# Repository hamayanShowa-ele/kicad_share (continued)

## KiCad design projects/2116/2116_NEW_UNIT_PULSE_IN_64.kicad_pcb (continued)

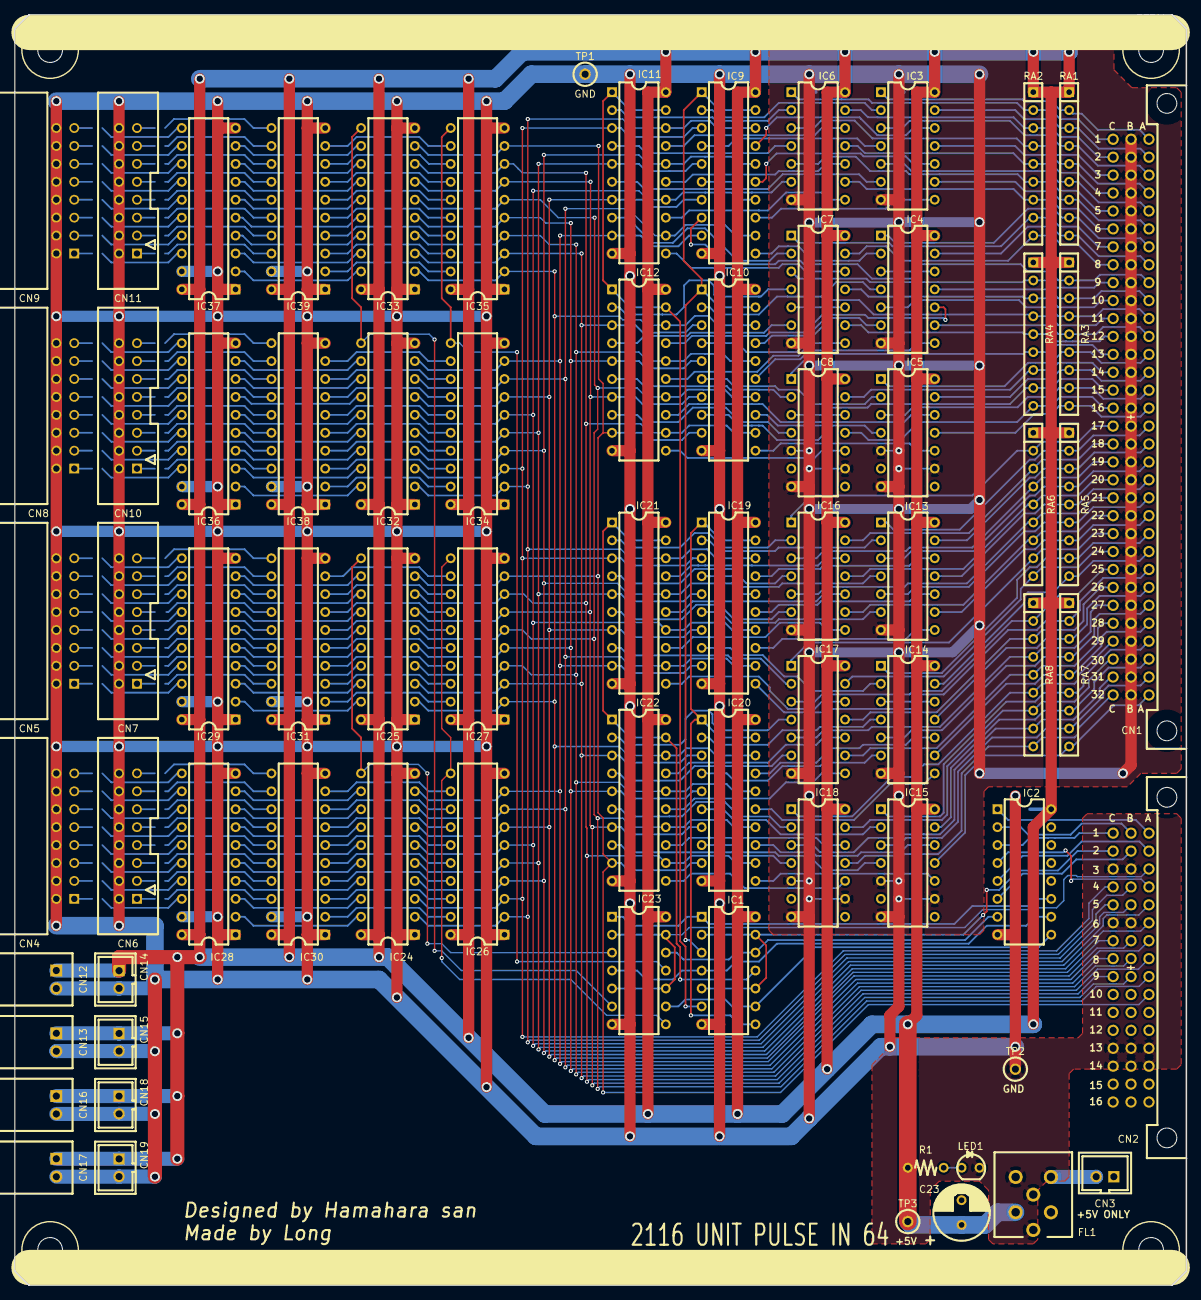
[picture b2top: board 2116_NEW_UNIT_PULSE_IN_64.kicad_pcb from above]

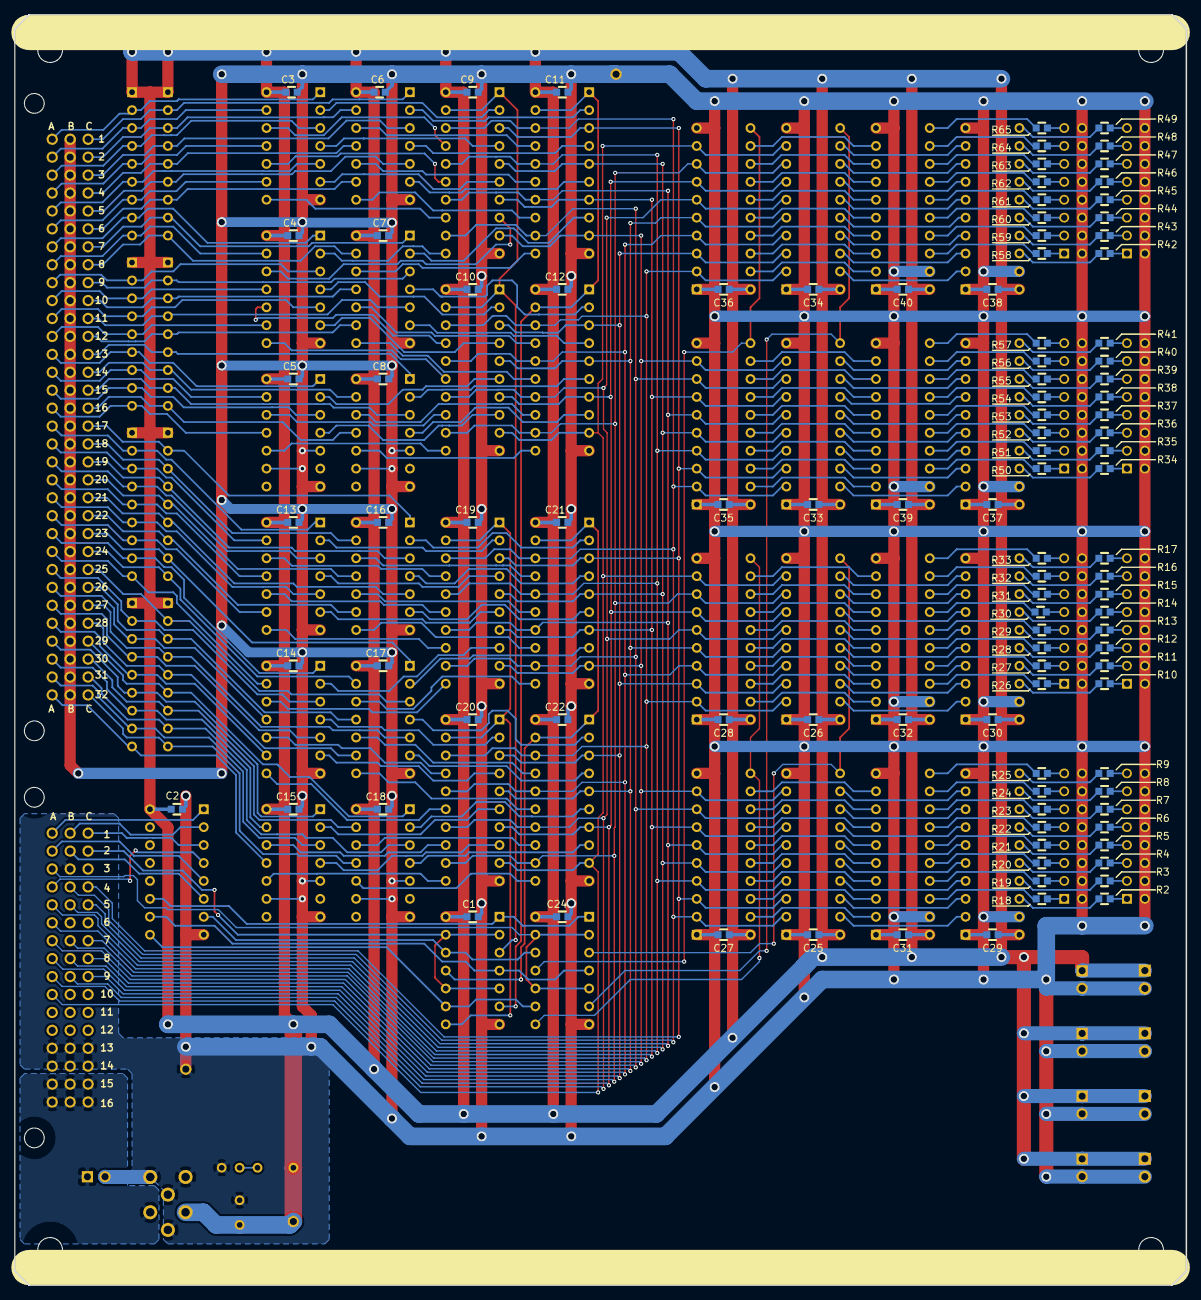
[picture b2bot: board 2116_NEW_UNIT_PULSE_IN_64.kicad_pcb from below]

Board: 2 copper layers, 166.0 x 180.0 mm, 176 parts (103 on the bottom side), 360 nets.

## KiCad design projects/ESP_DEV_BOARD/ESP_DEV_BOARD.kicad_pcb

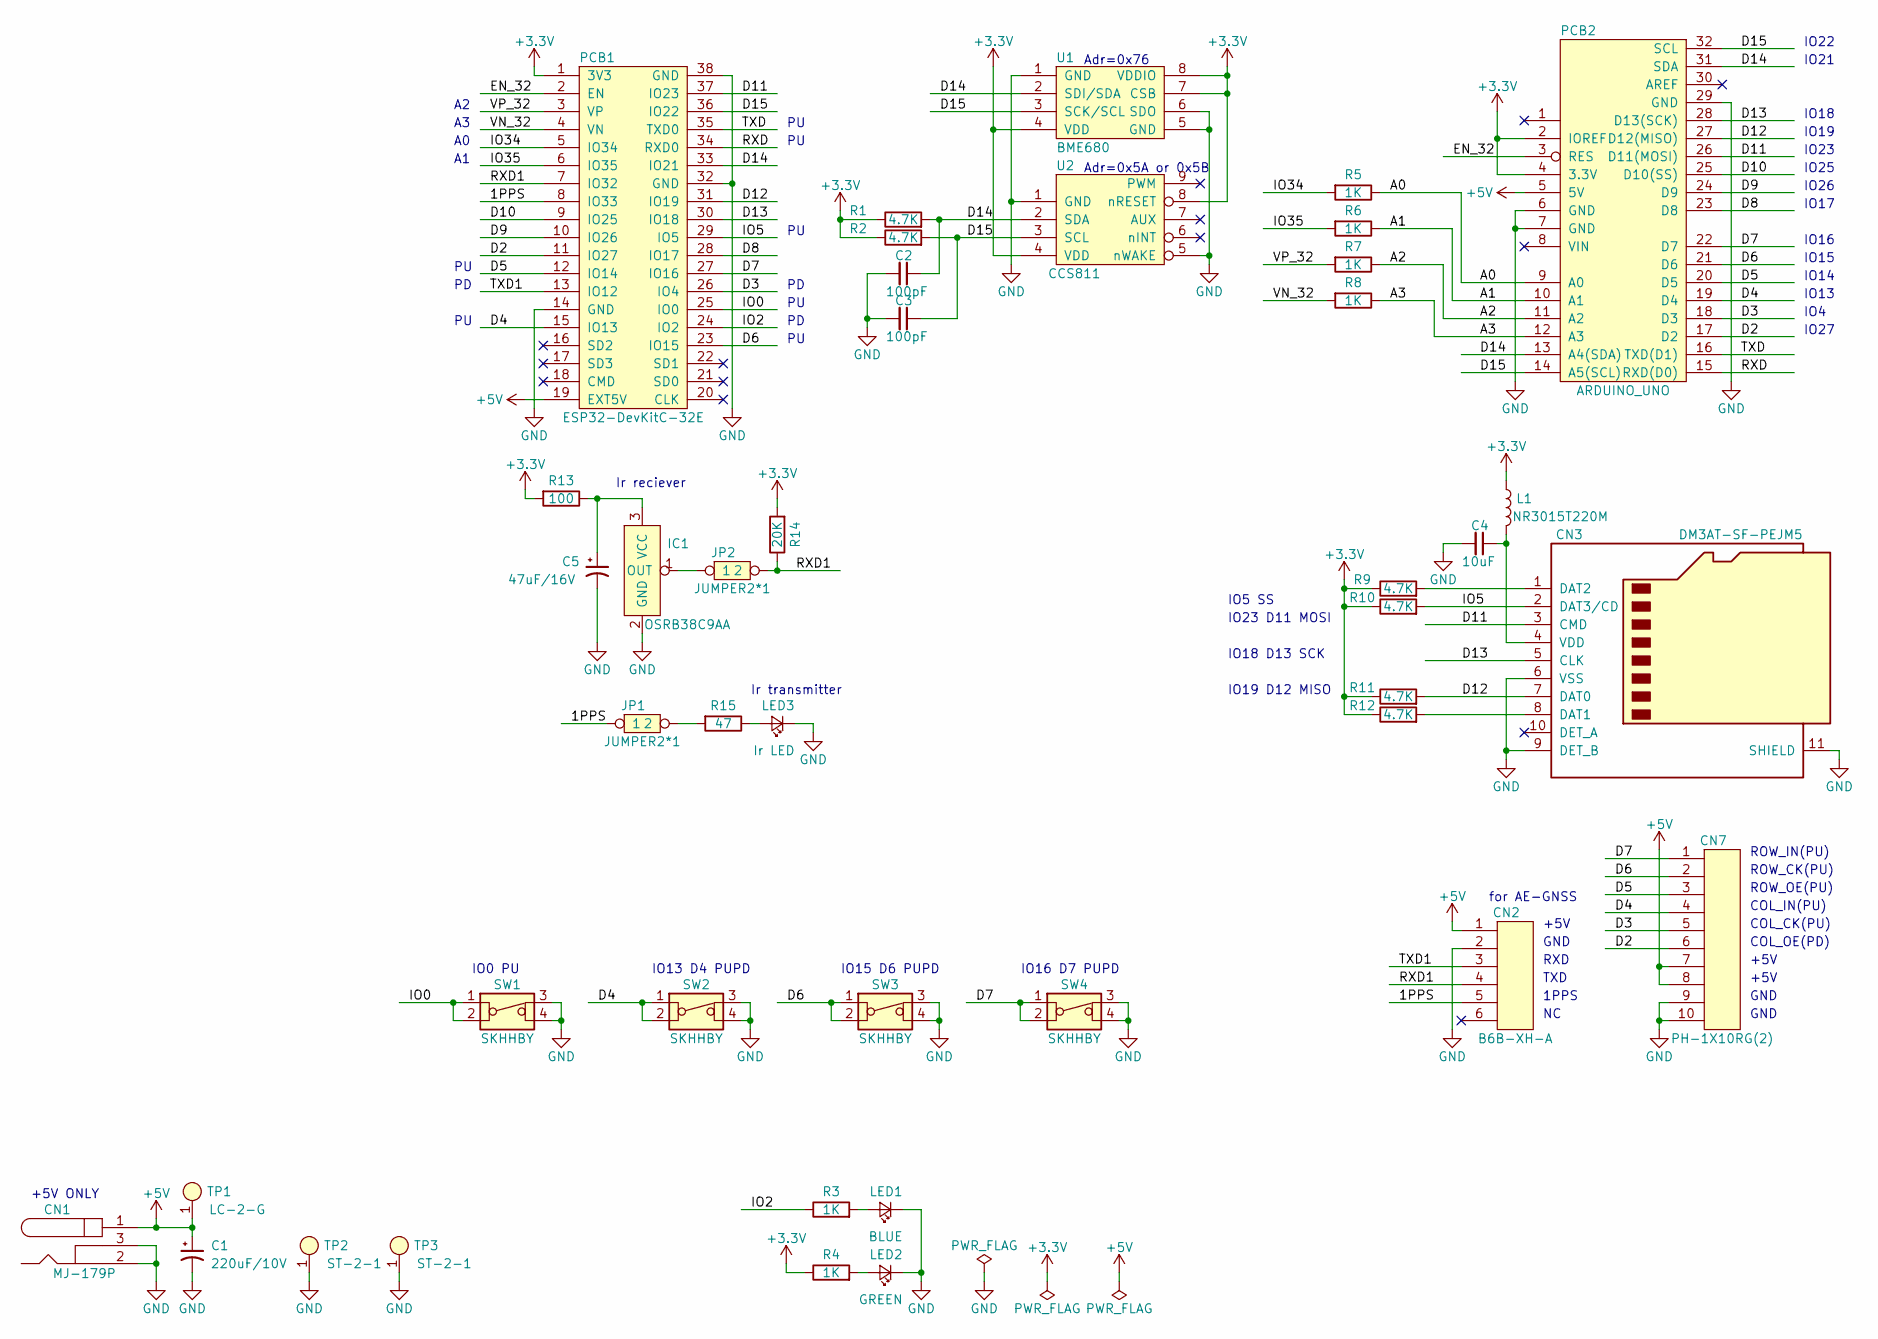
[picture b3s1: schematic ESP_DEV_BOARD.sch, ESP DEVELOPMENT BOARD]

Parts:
C1: 220uF/10V; CP_Radial_D8.25mm_P3.80mm
C2, C3: 100pF; C_0603
C4: 10uF; C_0805
C5: 47uF/16V; CP_Radial_D5.0mm_P2.00mm
CN1: MJ-179P
CN2: B6B-XH-A; cn_B6B-XH-A
CN3: DM3AT-SF-PEJM5; cn_DM3AT-SF-PEJM5
CN7: PH-1X10RG(2); cn_PH-1X10RG_2
IC1: OSRB38C9AA; ic_OSRB38C9AA
JP1, JP2: JUMPER2*1; JP_JUMPER1x2
L1: NR3015T220M; NR3010
LED1: BLUE; C_0603
LED2: GREEN; C_0603
LED3: Ir LED; led_5mmLED
PCB1: ESP32-DevKitC-32E; pcb_ESP32-DevKitC
PCB2: ARDUINO_UNO; pcb_ARDUINO_UNO
R1, R2, R9, R10, R11, R12: 4.7K; C_0603
R3, R4, R5, R6, R7, R8: 1K; C_0603
R13: 100; C_0603
R14: 20K; C_0603
R15: 47; C_0603
SW1, SW2, SW3, SW4: SKHHBY
TP1: LC-2-G
TP2, TP3: ST-2-1; LC-2-G
U1: BME680; pcb_BME680_strawberry-linux
U2: CCS811; pcb_CCS811_strawberry-linux

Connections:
+3V3: L1.1, PCB1.1 (3V3), PCB2.2 (IOREF), PCB2.4 (3.3V), R1.1, R2.1, R4.1, R9.1, R10.1, R11.1, R12.1, R13.2, R14.2, U1.4 (VDD), U1.7 (CSB), U1.8 (VDDIO), U2.4 (VDD), U2.8 (nRESET)
+5V: C1.1, CN1.1, CN2.1, CN7.7, CN7.8, PCB1.19 (EXT5V), PCB2.5 (5V), TP1.1
/1PPS: CN2.5, JP1.1, PCB1.8 (IO33)
/A0: PCB2.9 (A0), R5.1
/A1: PCB2.10 (A1), R6.1
/A2: PCB2.11 (A2), R7.1
/A3: PCB2.12 (A3), R8.1
/D2: CN7.6, PCB1.11 (IO27), PCB2.17 (D2)
/D3: CN7.5, PCB1.26 (IO4), PCB2.18 (D3)
/D4: CN7.4, PCB1.15 (IO13), PCB2.19 (D4), SW2.1, SW2.2
/D5: CN7.3, PCB1.12 (IO14), PCB2.20 (D5)
/D6: CN7.2, PCB1.23 (IO15), PCB2.21 (D6), SW3.1, SW3.2
/D7: CN7.1, PCB1.27 (IO16), PCB2.22 (D7), SW4.1, SW4.2
/D8: PCB1.28 (IO17), PCB2.23 (D8)
/D9: PCB1.10 (IO26), PCB2.24 (D9)
/D10: PCB1.9 (IO25), PCB2.25 (D10(SS))
/D11: CN3.3 (CMD), PCB1.37 (IO23), PCB2.26 (D11(MOSI))
/D12: CN3.7 (DAT0), PCB1.31 (IO19), PCB2.27 (D12(MISO)), R11.2
/D13: CN3.5 (CLK), PCB1.30 (IO18), PCB2.28 (D13(SCK))
/D14: C2.1, PCB1.33 (IO21), PCB2.13 (A4(SDA)), PCB2.31 (SDA), R1.2, U1.2 (SDI/SDA), U2.2 (SDA)
/D15: C3.1, PCB1.36 (IO22), PCB2.14 (A5(SCL)), PCB2.32 (SCL), R2.2, U1.3 (SCK/SCL), U2.3 (SCL)
/EN_32: PCB1.2 (EN), PCB2.3 (RES)
/IO0: PCB1.25 (IO0), SW1.1, SW1.2
/IO2: PCB1.24 (IO2), R3.1
/IO5: CN3.2 (DAT3/CD), PCB1.29 (IO5), R10.2
/IO34: PCB1.5 (IO34), R5.2
/IO35: PCB1.6 (IO35), R6.2
/RXD: PCB1.34 (RXD0), PCB2.15 (RXD(D0))
/RXD1: CN2.4, JP2.2, PCB1.7 (IO32), R14.1
/TXD: PCB1.35 (TXD0), PCB2.16 (TXD(D1))
/TXD1: CN2.3, PCB1.13 (IO12)
/VN_32: PCB1.4 (VN), R8.2
/VP_32: PCB1.3 (VP), R7.2
GND: C1.2, C2.2, C3.2, C4.2, C5.2, CN1.2, CN1.3, CN2.2, CN3.6 (VSS), CN3.9 (DET_B), CN3.11 (SHIELD), CN7.9, CN7.10, IC1.2 (GND), LED1.2 (K), LED2.2 (K), LED3.2 (K), PCB1.14 (GND), PCB1.32 (GND), PCB1.38 (GND), PCB2.6 (GND), PCB2.7 (GND), PCB2.29 (GND), SW1.3, SW1.4, SW2.3, SW2.4, SW3.3, SW3.4, SW4.3, SW4.4, TP2.1, TP3.1, U1.1 (GND), U1.5 (GND), U1.6 (SDO), U2.1 (GND), U2.5 (nWAKE)
unnamed: C4.1, CN3.4 (VDD), L1.2
unnamed: C5.1, IC1.3 (VCC), R13.1
unnamed: CN3.1 (DAT2), R9.2
unnamed: CN3.8 (DAT1), R12.2
unnamed: IC1.1 (OUT), JP2.1
unnamed: JP1.2, R15.2
unnamed: LED1.1 (A), R3.2
unnamed: LED2.1 (A), R4.2
unnamed: LED3.1 (A), R15.1

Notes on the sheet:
+5V ONLY
ROW_IN(PU)
ROW_CK(PU)
ROW_OE(PU)
COL_IN(PU)
COL_CK(PU)
COL_OE(PD)
+5V
GND
IO16
IO22
IO19
IO21
IO18
IO23
IO25
IO26
IO17
IO15
IO14
IO13
IO4
IO27
IO18 D13 SCK
IO19 D12 MISO
IO23 D11 MOSI
IO5 SS
IO16 D7 PUPD
IO15 D6 PUPD
IO13 D4 PUPD
IO0 PU
Adr=0x76
Adr=0x5A or 0x5B
+5V
RXD
TXD
1PPS
for AE-GNSS
Ir reciever
Ir transmitter

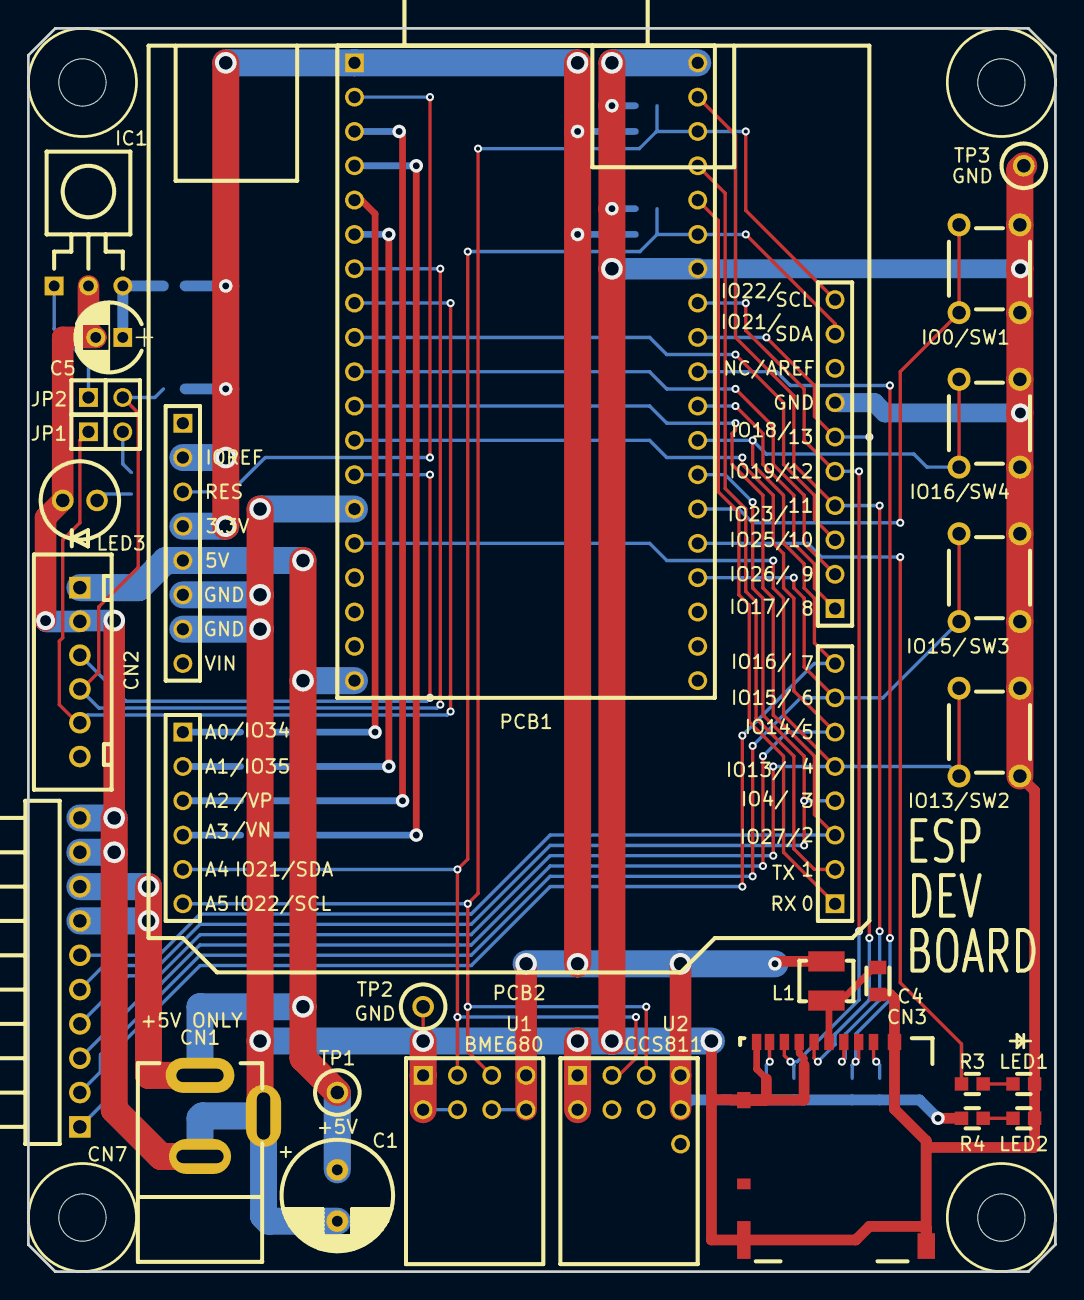
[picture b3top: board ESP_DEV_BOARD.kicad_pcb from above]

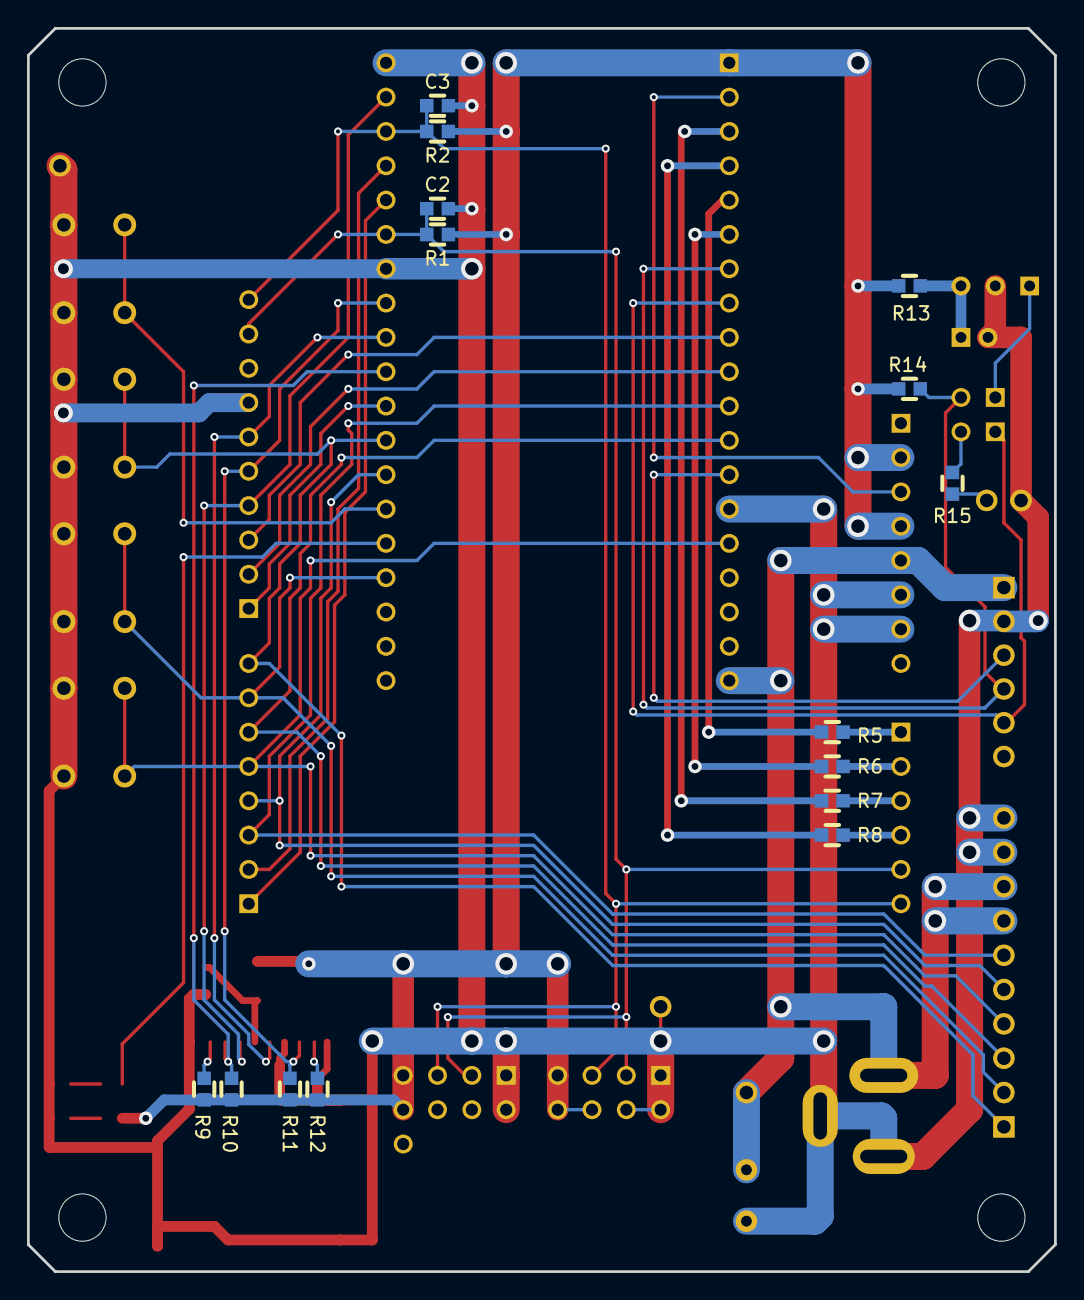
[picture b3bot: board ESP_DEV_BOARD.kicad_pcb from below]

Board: 2 copper layers, 76.0 x 92.0 mm, 42 parts (15 on the bottom side), 43 nets.

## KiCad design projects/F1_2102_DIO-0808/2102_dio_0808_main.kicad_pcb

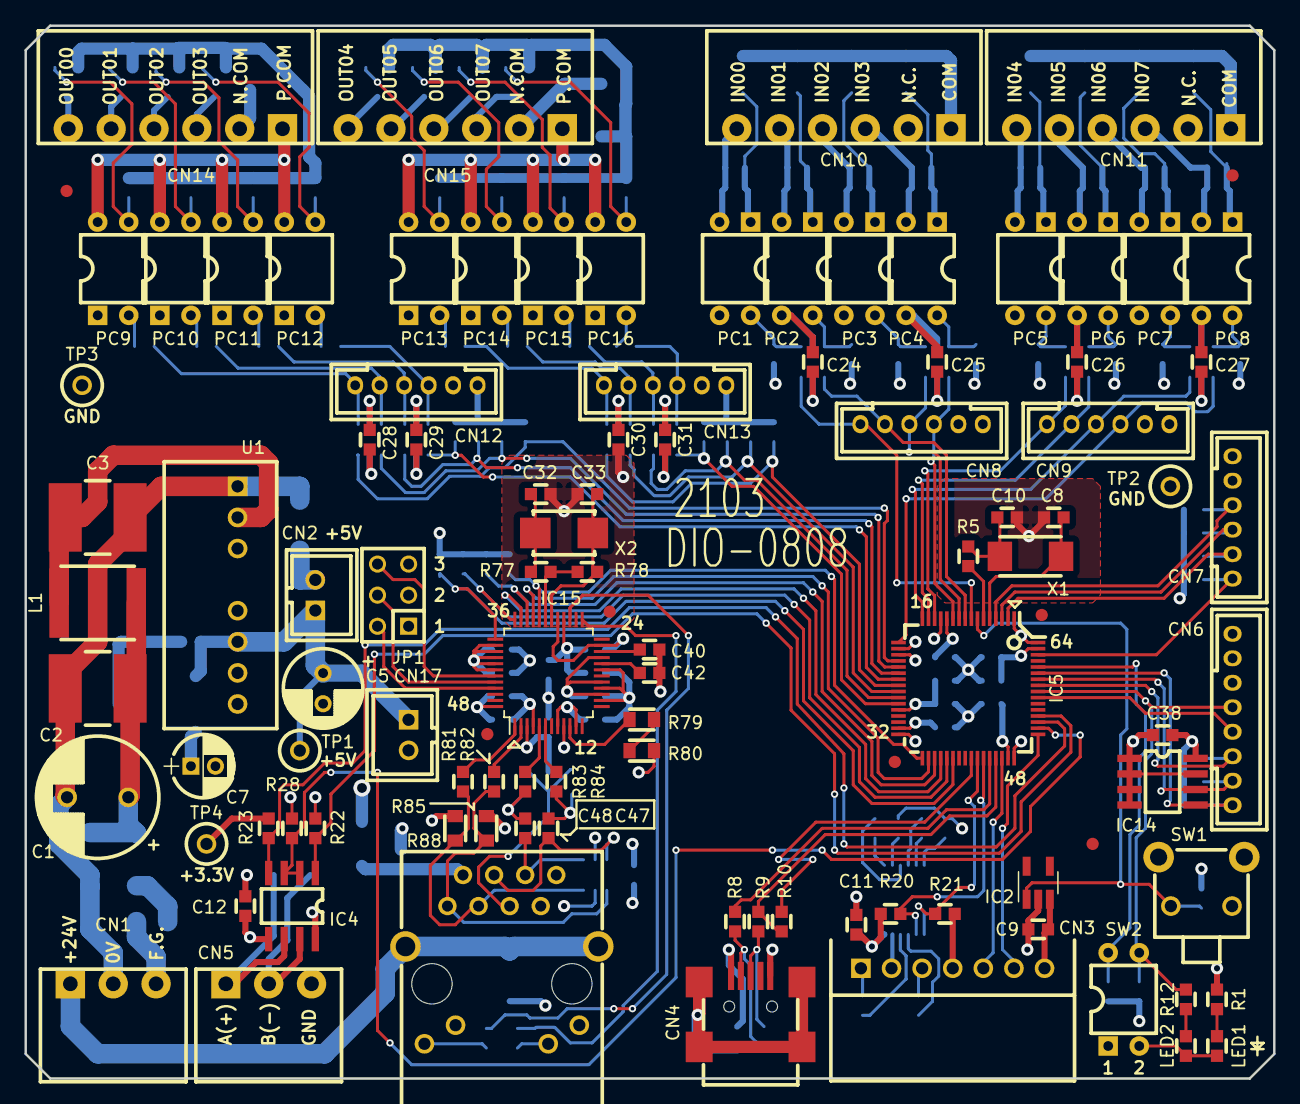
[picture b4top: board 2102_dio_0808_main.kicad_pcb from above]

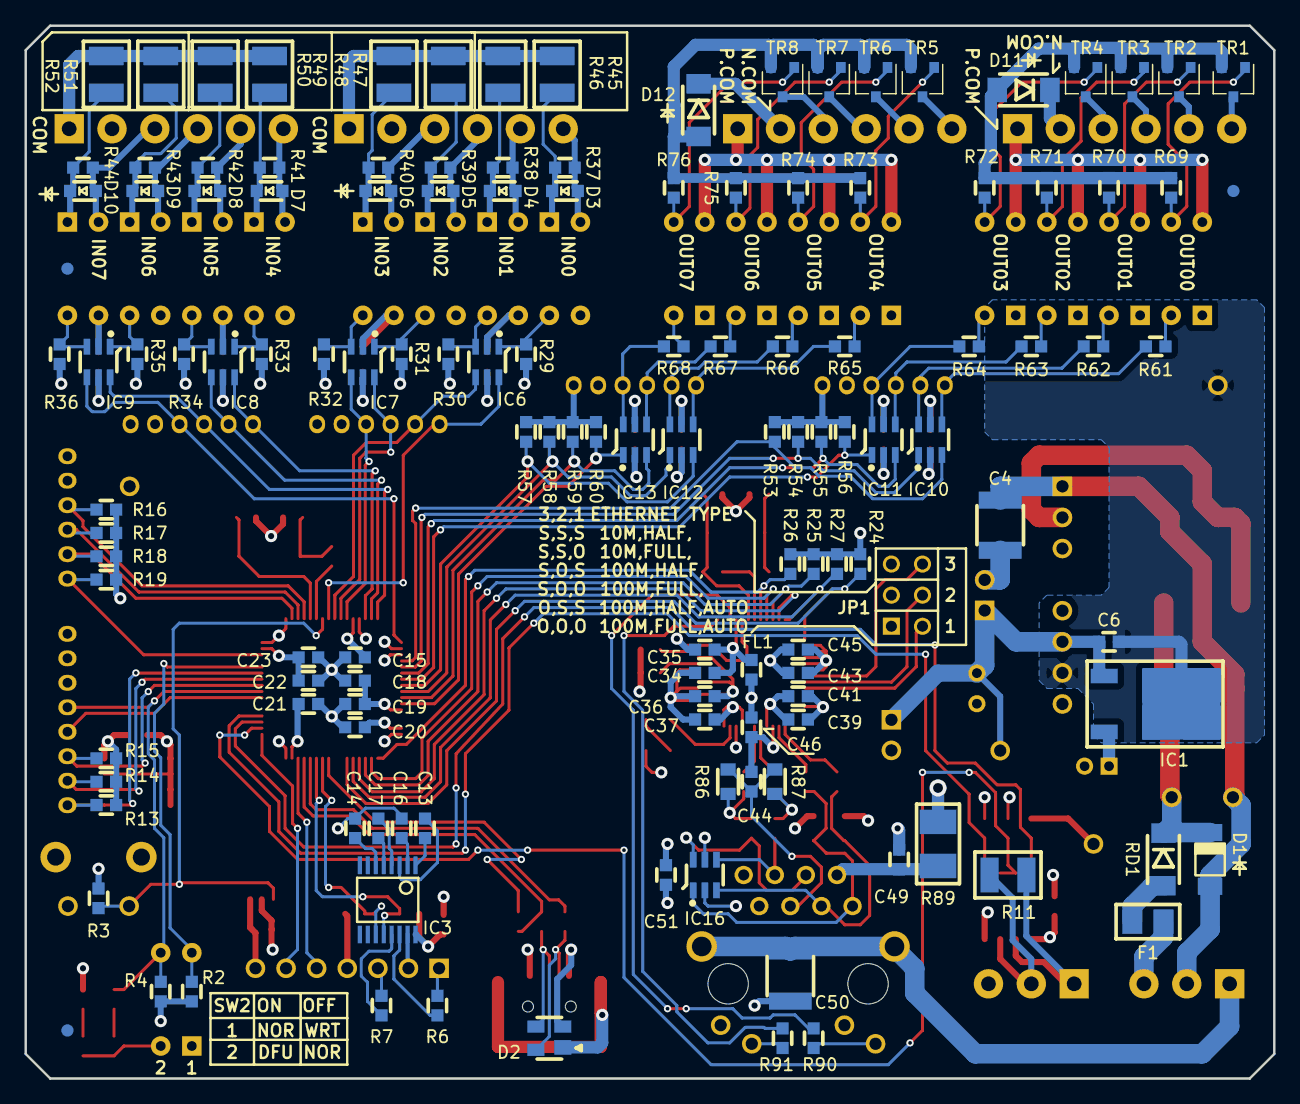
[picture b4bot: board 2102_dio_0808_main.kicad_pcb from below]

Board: 4 copper layers, 102.0 x 86.0 mm, 227 parts (130 on the bottom side), 164 nets.

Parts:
C1: 470uF/35V; CP_Radial_D10.0mm_P5.00mm
C2, C3: 22uF/50V; c_KRM55TR71H226MH01K
C4: 150pF/3KV; c_4532
C5: 220uF/10V; CP_Radial_D6.50mm_P2.50mm
C6, C11, C12, C13, C14, C15, C16, C17, C18, C19, C20, C21, C22, C24, C25, C26, C27, C28, C29, C30, C31, C35, C36, C37, C38, C39, C41, C43, C45, C51: 0.1uF; C_0603
C7: 22uF/16V; CP_Radial_D5.0mm_P2.00mm
C8, C10: 10pF; C_0603
C9: 1uF; C_0603
C23, C34, C42, C46: 4.7uF; C_0603
C32, C33: 13pF; C_0603
C40, C44: 0.01uF; C_0603
C47, C48: 6800pF; C_0603
C49: 22000pF; C_0603
C50: 1000pF/3kV; c_4532
CN1, CN5: 1844223; cn_1844223
CN2, CN17: B2B-XH-A; cn_B2B-XH-A
CN3: S7B-XH-A; cn_S7B-XH-A
CN4: UX60A-MB-5ST; cn_UX60-MB-5ST
CN6: B8B-PH-K-S; cn_B8B-PH-K-S
CN7, CN8, CN9, CN12, CN13: B6B-PH-K-S; cn_B6B-PH-K-S
CN10, CN11, CN14, CN15: 1844252; cn_1844252
CN16: J1B1211CCD
D1, D11, D12: SX34F; d_SX34F
D2: SP0503BAHTG; d_SP0503BAHT
D3, D4, D5, D6, D7, D8, D9, D10: 1SS355; d_1SS355
F1: 0.25A; C_3216
FL1: BLM18PG121SN1D; C_0603
IC1: NJM2391DL1; TO-252-2
IC2: PST8228NR; SOT-23-5_HandSoldering
IC3: ICL3232CVZ; IC_TSSOP-16
IC4: ISL83485IBZ; SOIC-8
IC5: STM32F103RET; ic_LQFP-64_10x10mm_Pitch0.5mm
IC6, IC7, IC8, IC9, IC10, IC11, IC12, IC13: SN74LVC2G14DBVR; SOT-23-6
IC14: 24AA025E48T; SOIC-8
IC15: W5500; ic_LQFP-48_7x7mm_Pitch0.5mm
IC16: TPD4E1U06DBVR; SOT-23-6
JP1: JUMPER 2*6; jp_JUMPER3x2
L1: 3uH; l_NR6028
LED1: GREEN; C_0603
LED2: BLUE; C_0603
PC1, PC2, PC3, PC4, PC5, PC6, PC7, PC8, PC9, PC10, PC11, PC12, PC13, PC14, PC15, PC16: VO618A-4X016; ic_DIP-4_W7.62mm
R1, R90, R91: 470; C_0603
R2, R3, R4, R13, R14, R15: 4.7K; C_0603
R5, R77, R81, R82, R83, R84: 0; C_0603
R6, R7: 100; C_0603
R8, R9: 27; C_0603
R10: 1.5K; C_0603
R11: 100; RGC325
R12: 1K; C_0603
R16, R17, R18, R19, R20, R21, R22, R23, R24, R25, R26, R27, R69, R70, R71, R72, R73, R74, R75, R76: 10K; C_0603
R28, R53, R54, R55, R56, R57, R58, R59, R60: 100K; C_0603
R29, R30, R31, R32, R33, R34, R35, R36: 3.3K; C_0603
R37, R38, R39, R40, R41, R42, R43, R44: 2.7K; C_0603
R45, R46, R47, R48, R49, R50, R51, R52: 15K; RGC325
R61, R62, R63, R64, R65, R66, R67, R68: 1.2K; C_0603
R78: 1M; C_0603
R79: 12K; C_0805
R80: 300; C_0805
R85, R88: 49.9; C_0805
R86, R87: 82; C_0805
R89: 10 1/4W; r_RGC3528
RD1: PDZVTFTR33B; SOD128
SW1: EQV-PC305K; sw_EQVPC
SW2: A6TR-2104; ic_DIP-4_W7.62mm
TP1, TP4: LC-2-G
TP2, TP3: ST-2-1; LC-2-G
TR1, TR2, TR3, TR4, TR5, TR6, TR7, TR8: 2SC3325; SC-59
U1: RSE-2405SZ/H2; u_RSE-2405SZ_H2
X1: NX5032GA 8MHz; x_NX5032GA
X2: ABM3-25.000MHz; x_ABM3-25M

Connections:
+3.3VA: C36.1, C37.1, C39.1, C41.1, C43.1, C45.1, C46.1, C51.1, CN16.10, CN16.12, FL1.2, IC15.4, IC15.8, IC15.11, IC15.15, IC15.17, IC15.21, IC16.5, R85.1, R88.1, R89.1
+3V3: C7.1, C9.1, C11.1, C12.1, C15.1, C18.1, C19.1, C20.1, C21.1, C22.1, C23.1, C24.1, C25.1, C26.1, C27.1, C28.1, C29.1, C30.1, C31.1, C34.1, C35.1, C38.1, CN3.4, CN6.7, CN7.5, CN8.5, CN9.5, CN12.5, CN13.5, FL1.1, IC1.3, IC2.2, IC3.16, IC4.8, IC5.1, IC5.13, IC5.19, IC5.32, IC5.48, IC5.64, IC6.5, IC7.5, IC8.5, IC9.5, IC10.5, IC11.5, IC12.5, IC13.5, IC14.8, IC15.28, PC9.1, PC10.1, PC11.1, PC12.1, PC13.1, PC14.1, PC15.1, PC16.1, R1.1, R2.1, R3.1, R4.1, R13.1, R14.1, R15.1, R16.1, R17.1, R18.1, R19.1, R20.1, R21.1, R22.1, R23.1, R24.1, R25.1, R26.1, R27.1, R29.1, R30.1, R31.1, R32.1, R33.1, R34.1, R35.1, R36.1, TP4.1
+5V: C5.1, C6.1, CN2.1, CN17.1, IC1.1, TP1.1, U1.6
/ETHERNET/ACTLED: IC15.27, R90.1
/ETHERNET/LINKLED: IC15.25, R91.1
/ETHERNET/PMODE0: IC15.45, JP1.6
/ETHERNET/PMODE1: IC15.44, JP1.5
/ETHERNET/PMODE2: IC15.43, JP1.4
/ETHERNET/RD+: C47.1, CN16.4, IC16.6
/ETHERNET/RD-: C48.1, CN16.6, IC16.4
/ETHERNET/RXN: C48.2, R83.2, R87.2
/ETHERNET/RXP: C47.2, R84.2, R86.2
/ETHERNET/SCL1: CN6.2, IC5.58, IC14.6, R14.2
/ETHERNET/SDA1: CN6.1, IC5.59, IC14.5, R13.2
/ETHERNET/SPI2_MISO: IC5.35, IC15.34, R25.2
/ETHERNET/SPI2_MOSI: IC5.36, IC15.35
/ETHERNET/SPI2_SCK: IC5.34, IC15.33
/ETHERNET/TXN: CN16.3, IC16.3, R81.2, R88.2
/ETHERNET/TXP: CN16.1, IC16.1, R82.2, R85.2
/ETHERNET/W5500_CS: IC5.33, IC15.32, R26.2
/ETHERNET/W5500_INT: IC5.37, IC15.36, R27.2
/ETHERNET/W5500_RST: IC5.38, IC15.37, R24.2
/PULSE_INPUT/IN00: CN8.1, IC5.8, IC6.6
/PULSE_INPUT/IN01: CN8.2, IC5.9, IC6.4
/PULSE_INPUT/IN02: CN8.3, IC5.10, IC7.6
/PULSE_INPUT/IN03: CN8.4, IC5.11, IC7.4
/PULSE_INPUT/IN04: CN9.1, IC5.14, IC8.6
/PULSE_INPUT/IN05: CN9.2, IC5.15, IC8.4
/PULSE_INPUT/IN06: CN9.3, IC5.16, IC9.6
/PULSE_INPUT/IN07: CN9.4, IC5.17, IC9.4
/PULSE_INPUT/PCIN00: IC6.1, PC1.4, R29.2
/PULSE_INPUT/PCIN01: IC6.3, PC2.4, R30.2
/PULSE_INPUT/PCIN02: IC7.1, PC3.4, R31.2
/PULSE_INPUT/PCIN03: IC7.3, PC4.4, R32.2
/PULSE_INPUT/PCIN04: IC8.1, PC5.4, R33.2
/PULSE_INPUT/PCIN05: IC8.3, PC6.4, R34.2
/PULSE_INPUT/PCIN06: IC9.1, PC7.4, R35.2
/PULSE_INPUT/PCIN07: IC9.3, PC8.4, R36.2
/PULSE_INPUT/PIN00: CN10.6, D3.1, PC1.2, R37.2
/PULSE_INPUT/PIN01: CN10.5, D4.1, PC2.2, R38.2
/PULSE_INPUT/PIN02: CN10.4, D5.1, PC3.2, R39.2
/PULSE_INPUT/PIN03: CN10.3, D6.1, PC4.2, R40.2
/PULSE_INPUT/PIN04: CN11.6, D7.1, PC5.2, R41.2
/PULSE_INPUT/PIN05: CN11.5, D8.1, PC6.2, R42.2
/PULSE_INPUT/PIN06: CN11.4, D9.1, PC7.2, R43.2
/PULSE_INPUT/PIN07: CN11.3, D10.1, PC8.2, R44.2
/PULSE_OUTPUT/NOUT00: CN12.1, IC10.4, R61.1
/PULSE_OUTPUT/NOUT01: CN12.2, IC10.6, R62.1
/PULSE_OUTPUT/NOUT02: CN12.3, IC11.4, R63.1
/PULSE_OUTPUT/NOUT03: CN12.4, IC11.6, R64.1
/PULSE_OUTPUT/NOUT04: CN13.1, IC12.4, R65.1
/PULSE_OUTPUT/NOUT05: CN13.2, IC12.6, R66.1
/PULSE_OUTPUT/NOUT06: CN13.3, IC13.4, R67.1
/PULSE_OUTPUT/NOUT07: CN13.4, IC13.6, R68.1
/PULSE_OUTPUT/OUT00: IC5.20, IC10.3, R53.2
/PULSE_OUTPUT/OUT01: IC5.21, IC10.1, R54.2
/PULSE_OUTPUT/OUT02: IC5.22, IC11.3, R55.2
/PULSE_OUTPUT/OUT03: IC5.23, IC11.1, R56.2
/PULSE_OUTPUT/OUT04: IC5.24, IC12.3, R57.2
/PULSE_OUTPUT/OUT05: IC5.25, IC12.1, R58.2
/PULSE_OUTPUT/OUT06: IC5.26, IC13.3, R59.2
/PULSE_OUTPUT/OUT07: IC5.27, IC13.1, R60.2
/PULSE_OUTPUT/POUT00: CN14.6, TR1.3
/PULSE_OUTPUT/POUT01: CN14.5, TR2.3
/PULSE_OUTPUT/POUT02: CN14.4, TR3.3
/PULSE_OUTPUT/POUT03: CN14.3, TR4.3
/PULSE_OUTPUT/POUT04: CN15.6, TR5.3
/PULSE_OUTPUT/POUT05: CN15.5, TR6.3
/PULSE_OUTPUT/POUT06: CN15.4, TR7.3
/PULSE_OUTPUT/POUT07: CN15.3, TR8.3
/STM32F103xxx/ACT_LED: CN6.5, IC5.56, R4.2, R12.2, SW2.3
/STM32F103xxx/BOOT0: IC5.60, R2.2, SW2.4
/STM32F103xxx/DIO0: CN7.1, IC5.62, R19.2
/STM32F103xxx/DIO1: CN7.2, IC5.2, R18.2
/STM32F103xxx/DIO2: CN7.3, IC5.3, R17.2
/STM32F103xxx/DIO3: CN7.4, IC5.4, R16.2
/STM32F103xxx/LCD_RES: CN6.3, IC5.57, R15.2
/STM32F103xxx/OSC_IN: C8.1, IC5.5, X1.1
/STM32F103xxx/OSC_OUT: IC5.6, R5.1
/STM32F103xxx/RED_LED: CN6.4, IC5.55
/STM32F103xxx/RS_RXD1: IC3.13, R7.2
/STM32F103xxx/RS_TXD1: IC3.14, R6.2
/STM32F103xxx/RTS4: IC4.2, IC4.3, IC5.50, R28.2
/STM32F103xxx/RXD1: IC3.12, IC5.43, R20.2
/STM32F103xxx/RXD4: IC4.1, IC5.52, R22.2
/STM32F103xxx/SWCLK: CN3.6, IC5.49
/STM32F103xxx/SWDIO: CN3.5, IC5.46
/STM32F103xxx/TRX+: CN5.1, IC4.6, R11.1
/STM32F103xxx/TRX-: CN5.2, IC4.7, R11.2
/STM32F103xxx/TXD1: IC3.11, IC5.42, R21.2
/STM32F103xxx/TXD4: IC4.4, IC5.51, R23.2
/STM32F103xxx/USBDM: IC5.44, R8.2
/STM32F103xxx/USBDP: IC5.45, R9.2, R10.1
/STM32F103xxx/USBON: IC5.41, R10.2
/STM32F103xxx/nRESET: IC2.1, IC5.7, R3.2, SW1.1
Earth: C50.1, CN1.1, CN16.13, CN16.14
GND: C4.2, C5.2, C6.2, C7.2, C8.2, C9.2, C10.2, C11.2, C12.2, C14.2, C15.2, C16.2, C18.2, C19.2, C20.2, C21.2, C22.2, C23.2, C24.2, C25.2, C26.2, C27.2, C28.2, C29.2, C30.2, C31.2, C32.2, C33.2, C34.2, C35.2, C36.2, C37.2, C38.2, C39.2, C40.2, C41.2, C42.2, C43.2, C44.2, C45.2, C46.2, C49.2, C50.2, C51.2, CN2.2, CN3.2, CN3.7, CN4.5, CN5.3, CN6.8, CN7.6, CN8.6, CN9.6, CN12.6, CN13.6, CN16.8, CN17.2, IC1.2, IC2.3, IC3.15, IC4.5, IC5.12, IC5.18, IC5.28, IC5.31, IC5.47, IC5.63, IC6.2, IC7.2, IC8.2, IC9.2, IC10.2, IC11.2, IC12.2, IC13.2, IC14.1, IC14.2, IC14.3, IC14.4, IC14.7, IC15.3, IC15.9, IC15.14, IC15.16, IC15.19, IC15.23, IC15.29, IC15.38, IC15.39, IC15.40, IC15.41, IC15.42, IC15.48, IC16.2, JP1.1, JP1.2, JP1.3, LED1.2, LED2.2, PC1.3, PC2.3, PC3.3, PC4.3, PC5.3, PC6.3, PC7.3, PC8.3, R28.1, R53.1, R54.1, R55.1, R56.1, R57.1, R58.1, R59.1, R60.1, R80.2, SW1.2, SW2.1, SW2.2, TP2.1, TP3.1, U1.7
unnamed: C1.1, C2.1, D1.2, L1.1, RD1.2
unnamed: C1.2, C2.2, C3.2, C4.1, CN1.2, RD1.1, U1.1
unnamed: C3.1, L1.2, U1.2
unnamed: C10.1, R5.2, X1.2
unnamed: C13.1, IC3.1
unnamed: C13.2, IC3.3
unnamed: C14.1, IC3.6
unnamed: C16.1, IC3.2
unnamed: C17.1, IC3.4
unnamed: C17.2, IC3.5
unnamed: C32.1, R77.2, X2.1
unnamed: C33.1, IC15.30, R78.2, X2.2
unnamed: C40.1, IC15.22
unnamed: C42.1, IC15.20
unnamed: C44.1, CN16.5, R86.1, R87.1
unnamed: C49.1, CN16.2, R89.2
unnamed: CN1.3, F1.1
unnamed: CN3.1, R6.1
unnamed: CN3.3, R7.1
unnamed: CN4.1, D2.2
unnamed: CN4.2, D2.4, R8.1
unnamed: CN4.3, D2.3, R9.1
unnamed: CN4.6, D2.1
unnamed: CN10.1, R45.2, R46.2, R47.2, R48.2
unnamed: CN11.1, R49.2, R50.2, R51.2, R52.2
unnamed: CN14.1, PC9.4, PC10.4, PC11.4, PC12.4
unnamed: CN14.2, D11.2
unnamed: CN15.1, PC13.4, PC14.4, PC15.4, PC16.4
unnamed: CN15.2, D12.2
unnamed: CN16.9, R90.2
unnamed: CN16.11, R91.2
unnamed: D1.1, F1.2
unnamed: D3.2, PC1.1, R37.1, R45.1
unnamed: D4.2, PC2.1, R38.1, R46.1
unnamed: D5.2, PC3.1, R39.1, R47.1
unnamed: D6.2, PC4.1, R40.1, R48.1
unnamed: D7.2, PC5.1, R41.1, R49.1
unnamed: D8.2, PC6.1, R42.1, R50.1
unnamed: D9.2, PC7.1, R43.1, R51.1
unnamed: D10.2, PC8.1, R44.1, R52.1
unnamed: D11.1, R69.2, R70.2, R71.2, R72.2, TR1.2, TR2.2, TR3.2, TR4.2
unnamed: D12.1, R73.2, R74.2, R75.2, R76.2, TR5.2, TR6.2, TR7.2, TR8.2
unnamed: IC15.1, R81.1
unnamed: IC15.2, R82.1
unnamed: IC15.5, R83.1
unnamed: IC15.6, R84.1
unnamed: IC15.10, R79.1
unnamed: IC15.31, R77.1, R78.1
unnamed: LED1.1, R1.2
unnamed: LED2.1, R12.1
unnamed: PC9.2, R61.2
unnamed: PC9.3, R69.1, TR1.1
unnamed: PC10.2, R62.2
unnamed: PC10.3, R70.1, TR2.1
unnamed: PC11.2, R63.2
unnamed: PC11.3, R71.1, TR3.1
unnamed: PC12.2, R64.2
unnamed: PC12.3, R72.1, TR4.1
unnamed: PC13.2, R65.2
unnamed: PC13.3, R73.1, TR5.1
unnamed: PC14.2, R66.2
unnamed: PC14.3, R74.1, TR6.1
unnamed: PC15.2, R67.2
unnamed: PC15.3, R75.1, TR7.1
unnamed: PC16.2, R68.2
unnamed: PC16.3, R76.1, TR8.1
unnamed: R79.2, R80.1

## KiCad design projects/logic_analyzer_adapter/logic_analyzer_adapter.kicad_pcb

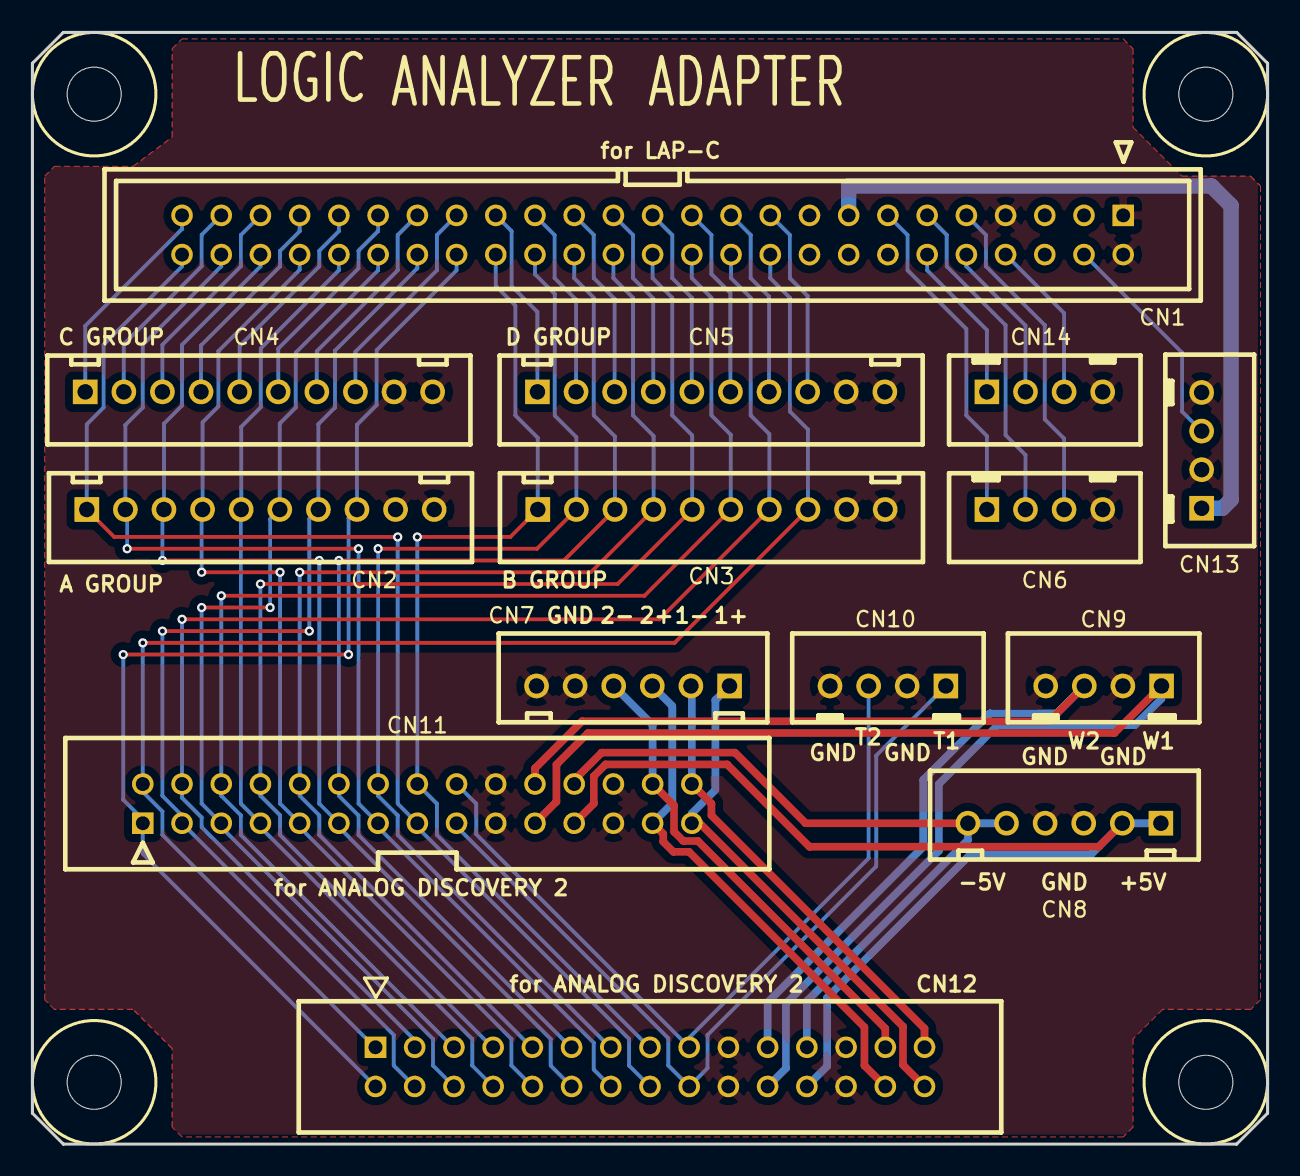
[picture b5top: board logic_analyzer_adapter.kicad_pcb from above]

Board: 2 copper layers, 80.0 x 72.0 mm, 14 parts (1 on the bottom side), 51 nets.

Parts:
CN1: LAP-C 50pin; cn_HIF3FC-50PA-2.54DSA
CN2, CN3, CN4, CN5: B10B-XH-A; cn_B10B-XH-A
CN6, CN9, CN10, CN13, CN14: B4B-XH-A; cn_B4B-XH-A
CN7, CN8: B6B-XH-A; cn_B6B-XH-A
CN11, CN12: DISCOVERY 30Pin; cn_HIF3FC-30PA-254DSA

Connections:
/A0: CN1.50, CN2.1, CN11.15, CN12.16
/A1: CN1.48, CN2.2, CN11.13, CN12.14
/A2: CN1.46, CN2.3, CN11.11, CN12.12
/A3: CN1.44, CN2.4, CN11.9, CN12.10
/A4: CN1.42, CN2.5, CN11.7, CN12.8
/A5: CN1.40, CN2.6, CN11.5, CN12.6
/A6: CN1.38, CN2.7, CN11.3, CN12.4
/A7: CN1.36, CN2.8, CN11.1, CN12.2
/ANALOG1+: CN7.1, CN11.29, CN12.30
/ANALOG1-: CN7.2, CN11.30, CN12.29
/ANALOG2+: CN7.3, CN11.27, CN12.28
/ANALOG2-: CN7.4, CN11.28, CN12.27
/B0: CN1.34, CN3.1, CN11.16, CN12.15
/B1: CN1.32, CN3.2, CN11.14, CN12.13
/B2: CN1.30, CN3.3, CN11.12, CN12.11
/B3: CN1.28, CN3.4, CN11.10, CN12.9
/B4: CN1.26, CN3.5, CN11.8, CN12.7
/B5: CN1.24, CN3.6, CN11.6, CN12.5
/B6: CN1.22, CN3.7, CN11.4, CN12.3
/B7: CN1.20, CN3.8, CN11.2, CN12.1
/C0: CN1.49, CN4.1
/C1: CN1.47, CN4.2
/C2: CN1.45, CN4.3
/C3: CN1.43, CN4.4
/C4: CN1.41, CN4.5
/C5: CN1.39, CN4.6
/C6: CN1.37, CN4.7
/C7: CN1.35, CN4.8
/CLK: CN1.4, CN13.3
/D0: CN1.33, CN5.1
/D1: CN1.31, CN5.2
/D2: CN1.29, CN5.3
/D3: CN1.27, CN5.4
/D4: CN1.25, CN5.5
/D5: CN1.23, CN5.6
/D6: CN1.21, CN5.7
/D7: CN1.19, CN5.8
/IOA: CN1.13, CN6.1
/IOB: CN1.11, CN6.2
/IOC: CN1.9, CN6.3
/R_O: CN1.12, CN14.1
/S_O: CN1.8, CN14.3
/TRG1: CN10.1, CN11.17, CN12.18
/TRG2: CN10.3, CN11.18, CN12.17
/T_O: CN1.10, CN14.2
/VCC: CN8.1, CN8.2, CN11.23, CN12.24
/VDD: CN1.15, CN13.1
/VSS: CN8.5, CN8.6, CN11.24, CN12.23
/WAVE1: CN9.1, CN11.21, CN12.22
/WAVE2: CN9.3, CN11.22, CN12.21
GND: CN1.1, CN1.2, CN1.7, CN2.9, CN2.10, CN3.9, CN3.10, CN4.9, CN4.10, CN5.9, CN5.10, CN6.4, CN7.5, CN7.6, CN8.3, CN8.4, CN9.2, CN9.4, CN10.2, CN10.4, CN11.19, CN11.20, CN11.25, CN11.26, CN12.19, CN12.20, CN12.25, CN12.26, CN13.2, CN13.4, CN14.4
